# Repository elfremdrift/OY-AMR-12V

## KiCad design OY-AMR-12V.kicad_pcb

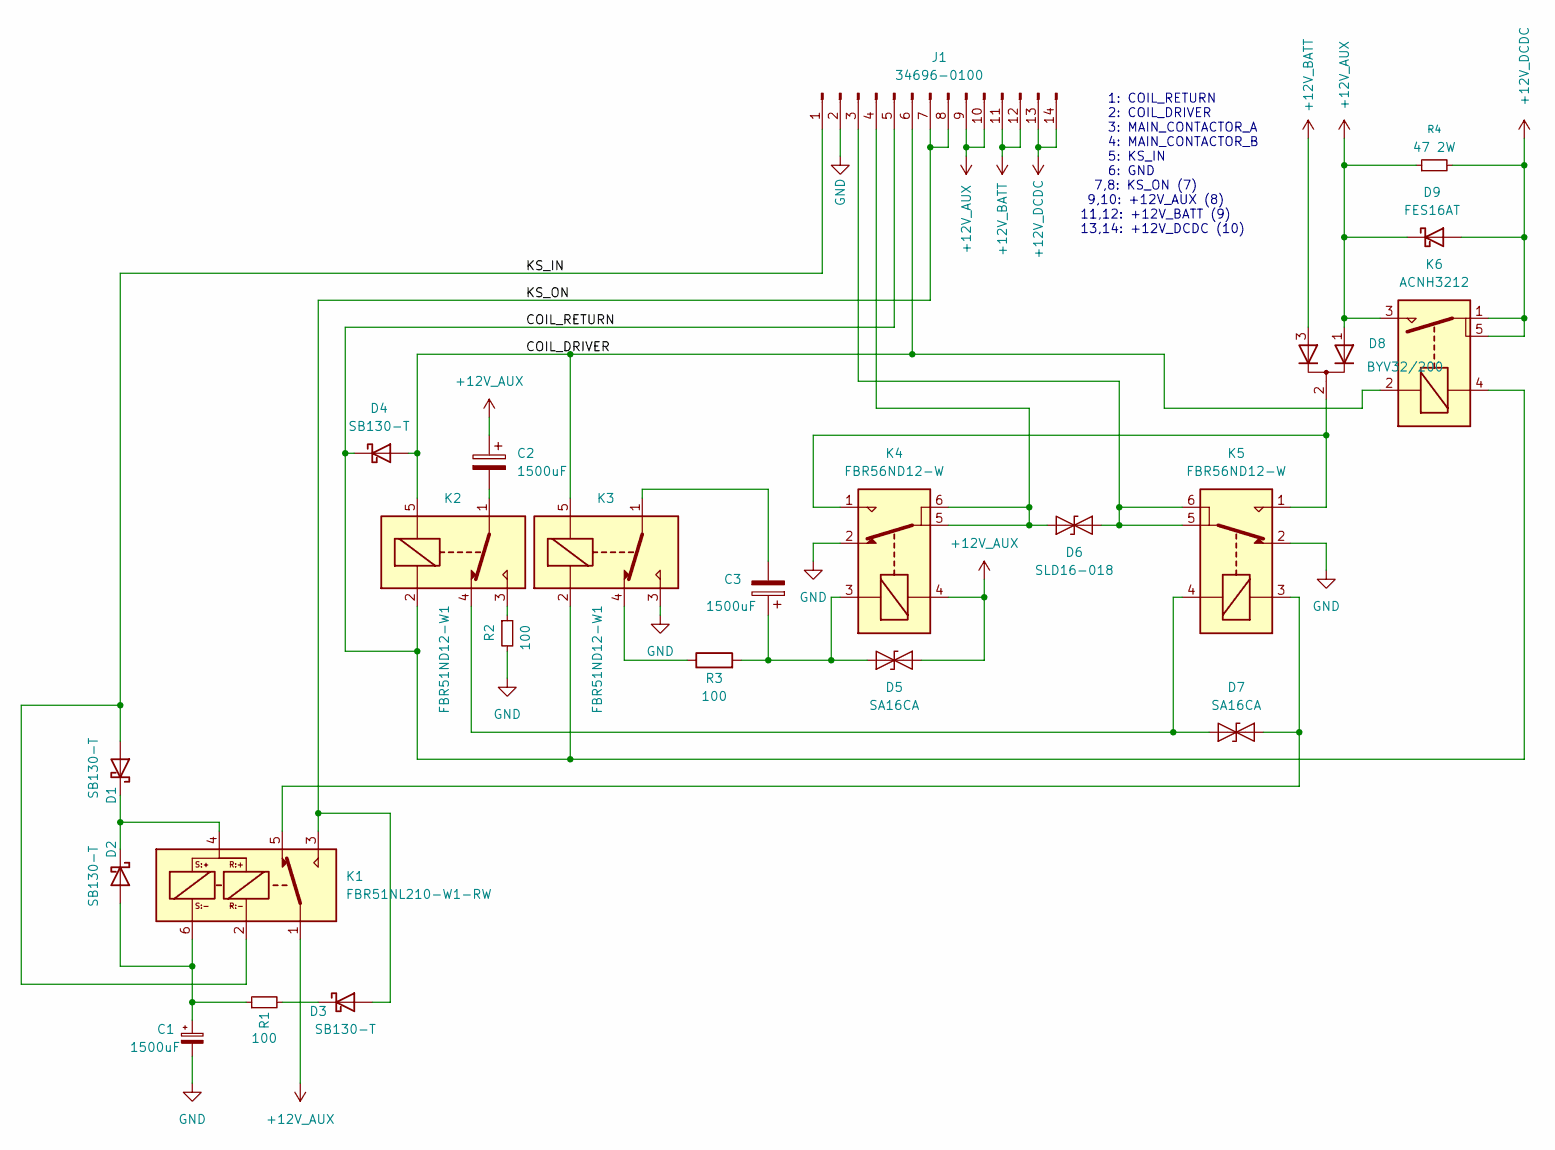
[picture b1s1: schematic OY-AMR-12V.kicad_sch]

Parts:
C1, C2, C3: 1500uF; CP_Radial_D16.0mm_P7.50mm
D1, D2, D3, D4: SB130-T; D_DO-41_SOD81_P10.16mm_Horizontal
D5, D7: SA16CA; D_T-1_P10.16mm_Horizontal
D6: SLD16-018; D_P600_R-6_P20.00mm_Horizontal
D8: BYV32/200; TO-220-3_Vertical
D9: FES16AT; TO-220-2_Vertical
J1: 34696-0100; 0346960100
K1: FBR51NL210-W1-RW; FBR51NL210W1RW
K2, K3: FBR51ND12-W1
K4, K5: FBR56ND12-W; FBR56ND12W
K6: ACNH3212
R1, R2, R3: 100; R_Axial_DIN0207_L6.3mm_D2.5mm_P10.16mm_Horizontal
R4: 47 2W; R_Axial_DIN0411_L9.9mm_D3.6mm_P15.24mm_Horizontal

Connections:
+12V_AUX: C2.1, D5.2 (A2), D8.1 (K), D9.1 (K), J1.9, J1.10, K1.1, K4.4, K6.3, R4.1
+12V_BATT: D8.3 (K), J1.11, J1.12
+12V_DCDC: D9.2 (A), J1.13, J1.14, K6.1, K6.5, R4.2
/COIL_DRIVER: D4.2 (A), J1.6, K2.5, K3.5, K6.2
/COIL_RETURN: D4.1 (K), J1.5, K2.2, K3.2, K6.4
/KS_IN: D1.2 (A), J1.1, K1.2
/KS_ON: D3.2 (A), J1.7, J1.8, K1.3
GND: C1.2, J1.2, K3.3, K4.2, K5.2, R2.2
unnamed: C2.2, K2.1
unnamed: C3.2, K3.1
unnamed: D1.1 (K), D2.1 (K), K1.4
unnamed: C1.1, D2.2 (A), K1.6, R1.1
unnamed: D3.1 (K), R1.2
unnamed: C3.1, D5.1 (A1), K4.3, R3.2
unnamed: D6.1 (A1), J1.4, K4.5, K4.6
unnamed: D6.2 (A2), J1.3, K5.5, K5.6
unnamed: D7.1 (A1), K2.4, K5.4
unnamed: D7.2 (A2), K1.5, K5.3
unnamed: D8.2 (A), K4.1, K5.1
unnamed: K2.3, R2.1
unnamed: K3.4, R3.1

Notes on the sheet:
1: COIL_RETURN 2: COIL_DRIVER 3: MAIN_CONTACTOR_A 4: MAIN_CONTACTOR_B 5: KS_IN 6: GND 7,8: KS_ON (7) 9,10: +12V_AUX (8) 11,12: +12V_BATT (9) 13,14: +12V_DCDC (10)

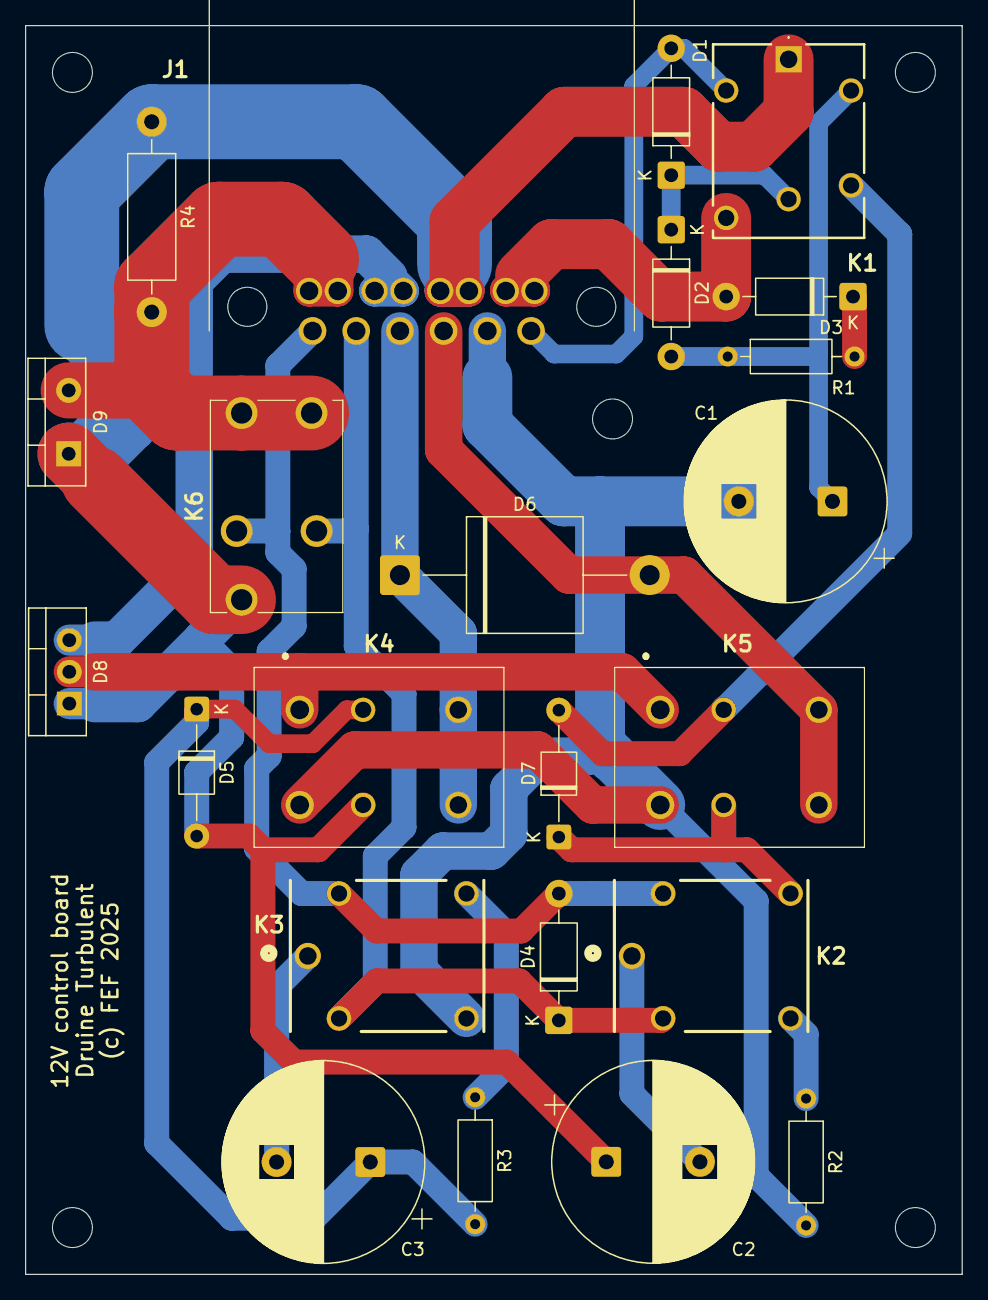
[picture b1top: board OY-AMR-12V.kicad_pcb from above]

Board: 2 copper layers, 75.0 x 100.0 mm, 28 parts (0 on the bottom side), 21 nets.

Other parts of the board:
MH1, MH2, MH3, MH4, MH5: MountingHole_3.2mm_M3_DIN965

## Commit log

2024-10-30 Initial commit (transistor version)
2024-10-30 Added standard libraries
2024-10-30 Added config for shared symbol and footprint libs
2024-10-30 Change to relay logic
2025-05-24 Relay-only version in progress
2025-06-04 Trying out bistable config options
2025-06-11 Re-implement with single-coil latching relays
2025-06-11 Component library upgrade
2025-08-04 Simplified & changed to available components
2025-08-06 Reduced schematics to PCB contents
2025-08-10 Added charging diode, connectors, revise latching relay type
2025-08-13 Updated DPDT relay to 2xSPDT automotive relays
2025-08-14 Upgraded to Kicad 9
2025-08-14 Added PDF of schematics
2025-08-15 Annotated and added footprints
2025-08-15 Initial PCB placements
2025-08-15 Added PDF export script
2025-08-15 Fix script file mode
2025-08-27 Added charge relay + precharge resistor for DC/DC
2025-08-27 PCB layout in progress
2025-08-28 Initial PCB layout
2025-08-30 PCB layout v0.1 ready for prototype production
2025-08-30 Added silk screen text
2025-08-30 Some Gerber settings
2025-09-03 Update connector text annotation
